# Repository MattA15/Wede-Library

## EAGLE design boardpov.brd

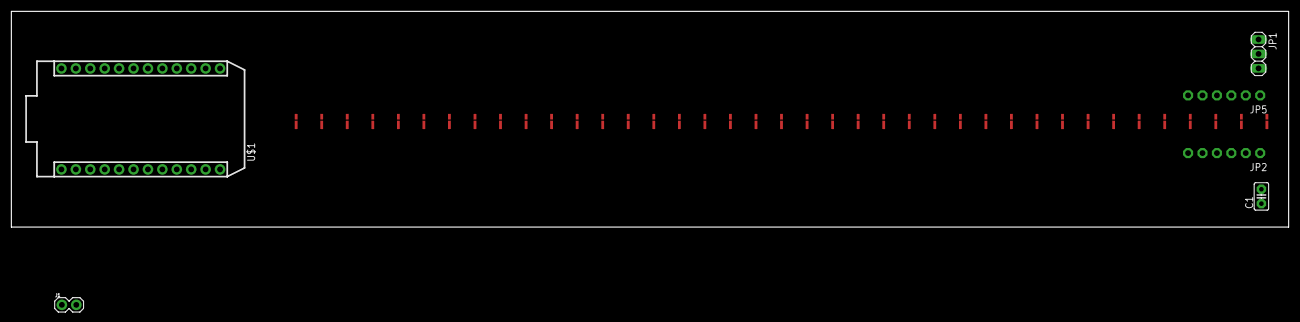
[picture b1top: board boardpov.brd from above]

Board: 2 copper layers, 225.0 x 38.0 mm, 45 parts (0 on the bottom side), 59 nets, no tracks yet.

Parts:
C1: C025-025X050
J1: 1X02
JP1: 1X03
JP2, JP5: 1X06-CLEANBIG
U$1: PHOTON_WITH_HEADERS; PHOTON
U$2, U$3, U$4, U$5, U$6, U$7, U$8, U$9, U$10, U$11, U$12, U$13, U$14, U$15, U$16, U$17, U$18, U$19, U$20, U$21, U$22, U$23, U$24, U$25, U$26, U$27, U$28, U$29, U$30, U$31, U$41, U$42, U$43, U$44, U$45, U$46, U$47, U$48, U$49: APA102-202020-20; APA102-2020

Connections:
unnamed: J1.2, U$1.1
unnamed: J1.1, U$1.2, U$1.21, U$2.GND, U$2.GND-, U$3.GND, U$3.GND-, U$4.GND, U$4.GND-, U$5.GND, U$5.GND-, U$6.GND, U$6.GND-, U$7.GND, U$7.GND-, U$8.GND, U$8.GND-, U$9.GND, U$9.GND-, U$10.GND, U$10.GND-, U$11.GND, U$11.GND-, U$12.GND, U$12.GND-, U$13.GND, U$13.GND-, U$14.GND, U$14.GND-, U$15.GND, U$15.GND-, U$16.GND, U$16.GND-, U$17.GND, U$17.GND-, U$18.GND, U$18.GND-, U$19.GND, U$19.GND-, U$20.GND, U$20.GND-, U$21.GND, U$21.GND-, U$22.GND, U$22.GND-, U$23.GND, U$23.GND-, U$24.GND, U$24.GND-, U$25.GND, U$25.GND-, U$26.GND, U$26.GND-, U$27.GND, U$27.GND-, U$28.GND, U$28.GND-, U$29.GND, U$29.GND-, U$30.GND, U$30.GND-, U$31.GND, U$31.GND-, U$41.GND, U$41.GND-, U$42.GND, U$42.GND-, U$43.GND, U$43.GND-, U$44.GND, U$44.GND-, U$45.GND, U$45.GND-, U$46.GND, U$46.GND-, U$47.GND, U$47.GND-, U$48.GND, U$48.GND-, U$49.GND, U$49.GND-
unnamed: U$2.VDD, U$2.VDD+, U$3.VDD, U$3.VDD+, U$4.VDD, U$4.VDD+, U$5.VDD, U$5.VDD+, U$6.VDD, U$6.VDD+, U$7.VDD, U$7.VDD+, U$8.VDD, U$8.VDD+, U$9.VDD, U$9.VDD+, U$10.VDD, U$10.VDD+, U$11.VDD, U$11.VDD+, U$12.VDD, U$12.VDD+, U$13.VDD, U$13.VDD+, U$14.VDD, U$14.VDD+, U$15.VDD, U$15.VDD+, U$16.VDD, U$16.VDD+, U$17.VDD, U$17.VDD+, U$18.VDD, U$18.VDD+, U$19.VDD, U$19.VDD+, U$20.VDD, U$20.VDD+, U$21.VDD, U$21.VDD+, U$22.VDD, U$22.VDD+, U$23.VDD, U$23.VDD+, U$24.VDD, U$24.VDD+, U$25.VDD, U$25.VDD+, U$26.VDD, U$26.VDD+, U$27.VDD, U$27.VDD+, U$28.VDD, U$28.VDD+, U$29.VDD, U$29.VDD+, U$30.VDD, U$30.VDD+, U$31.VDD, U$31.VDD+, U$41.VDD, U$41.VDD+, U$42.VDD, U$42.VDD+, U$43.VDD, U$43.VDD+, U$44.VDD, U$44.VDD+, U$45.VDD, U$45.VDD+, U$46.VDD, U$46.VDD+, U$47.VDD, U$47.VDD+, U$48.VDD, U$48.VDD+, U$49.VDD, U$49.VDD+
unnamed: U$48.SD1, U$49.SD0
unnamed: U$48.CKL, U$49.CK0
unnamed: U$47.CKL, U$48.CK0
unnamed: U$47.SD1, U$48.SD0
unnamed: U$46.SD1, U$47.SD0
unnamed: U$46.CKL, U$47.CK0
unnamed: U$45.CKL, U$46.CK0
unnamed: U$45.SD1, U$46.SD0
unnamed: U$44.CKL, U$45.CK0
unnamed: U$44.SD1, U$45.SD0
unnamed: U$26.SD1, U$44.SD0
unnamed: U$26.CKL, U$44.CK0
unnamed: U$26.SD0, U$27.SD1
unnamed: U$26.CK0, U$27.CKL
unnamed: U$27.CK0, U$28.CKL
unnamed: U$27.SD0, U$28.SD1
unnamed: U$28.CK0, U$29.CKL
unnamed: U$28.SD0, U$29.SD1
unnamed: U$29.CK0, U$30.CKL
unnamed: U$29.SD0, U$30.SD1
unnamed: U$30.SD0, U$31.SD1
unnamed: U$30.CK0, U$31.CKL
unnamed: U$25.SD1, U$31.SD0
unnamed: U$25.CKL, U$31.CK0
unnamed: U$20.CKL, U$21.CK0
unnamed: U$20.SD1, U$21.SD0
unnamed: U$21.SD1, U$22.SD0
unnamed: U$21.CKL, U$22.CK0
unnamed: U$22.CKL, U$23.CK0
unnamed: U$22.SD1, U$23.SD0
unnamed: U$23.SD1, U$24.SD0
unnamed: U$23.CKL, U$24.CK0
unnamed: U$24.CKL, U$25.CK0
unnamed: U$24.SD1, U$25.SD0
unnamed: U$14.SD1, U$20.CK0
unnamed: U$14.CKL, U$20.SD0
unnamed: U$14.CK0, U$15.CKL
unnamed: U$14.SD0, U$15.SD1
unnamed: U$15.CK0, U$16.CKL
unnamed: U$15.SD0, U$16.SD1
unnamed: U$16.CK0, U$17.CKL
unnamed: U$16.SD0, U$17.SD1
unnamed: U$17.CK0, U$18.CKL
unnamed: U$17.SD0, U$18.SD1
unnamed: U$18.CK0, U$19.CKL
unnamed: U$18.SD0, U$19.SD1
unnamed: U$13.SD1, U$19.SD0
unnamed: U$13.CKL, U$19.CK0
unnamed: U$8.CKL, U$9.CK0
unnamed: U$8.SD1, U$9.SD0
unnamed: U$9.SD1, U$10.SD0
unnamed: U$9.CKL, U$10.CK0
unnamed: U$10.CKL, U$11.CK0
unnamed: U$10.SD1, U$11.SD0
unnamed: U$11.SD1, U$12.SD0
unnamed: U$11.CKL, U$12.CK0

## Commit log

2017-10-24 wooor
2017-10-26 sdsd
2017-10-31 dwdw

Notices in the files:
parts and their libraries:
SparkFun-Connectors: Licensing: Creative Commons ShareAlike 4.0 International - https://creativecommons.org/licenses/by-sa/4.0
